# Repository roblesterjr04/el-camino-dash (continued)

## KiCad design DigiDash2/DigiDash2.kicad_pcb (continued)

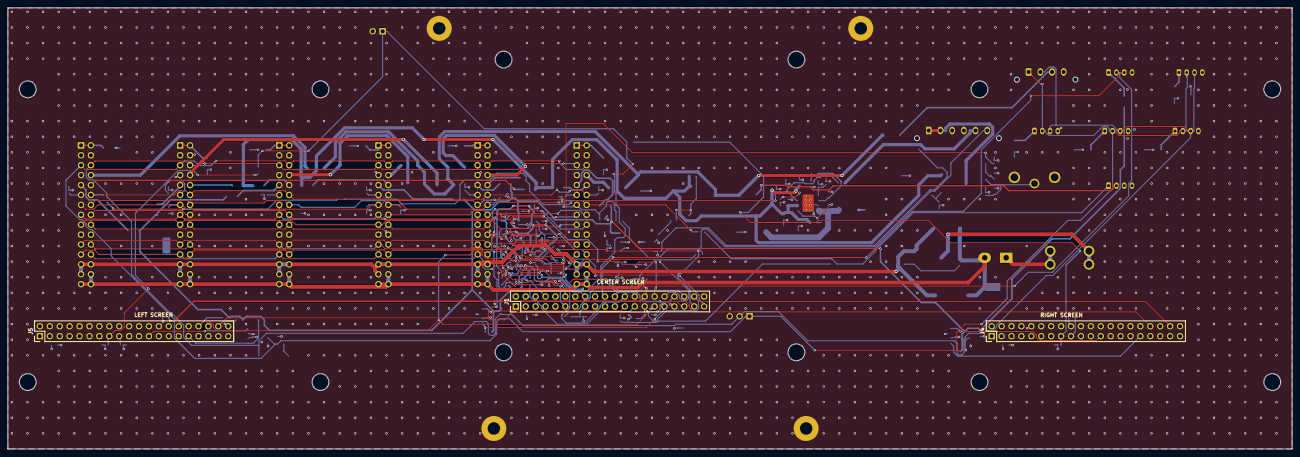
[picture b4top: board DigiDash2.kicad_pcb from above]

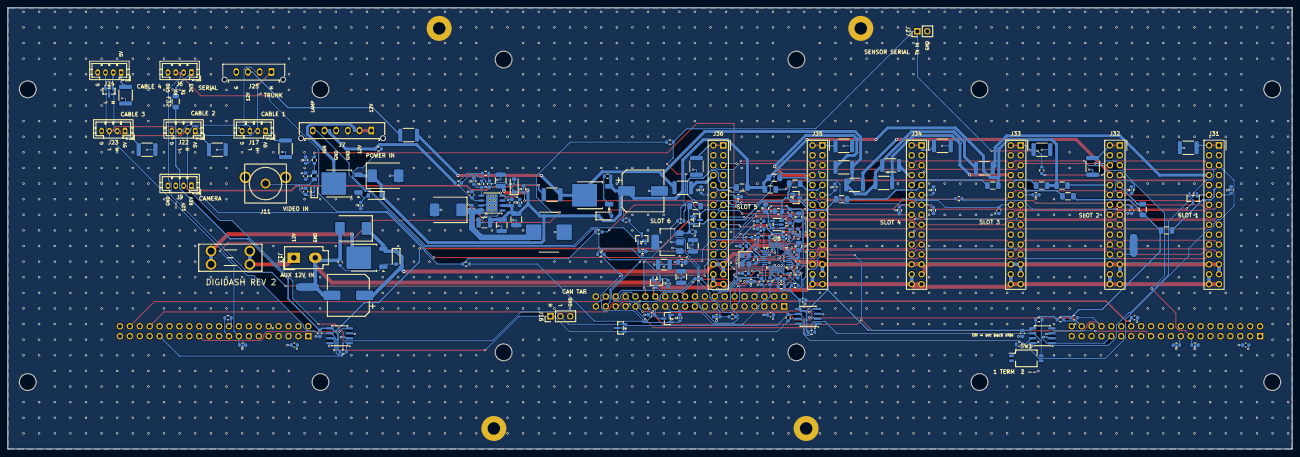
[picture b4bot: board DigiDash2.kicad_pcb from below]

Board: 4 copper layers, 329.0 x 113.0 mm, 197 parts (182 on the bottom side), 126 nets.

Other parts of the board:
H5, H6, H7, H8, H9, H10, H11, H12, H13, H14, H15, H16: M4 screen; MountingHole_4.3mm_M4

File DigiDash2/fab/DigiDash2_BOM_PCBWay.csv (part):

Item #,Designator,Qty,Manufacturer,Mfg Part #,Description / Value,Package/Footprint,Type,Side,Your Instructions / Notes
1,C1 C18,2,Honor,RYRVT63V100UF10*10,"100u 63V: Aluminium electrolytic 100 uF 63 V, SMD",10 x 10.2 mm SMD,SMD,Bottom,63 V: above the SMCJ33A clamp (about 53 V). Panasonic EEE-FK1J101P (AEC-Q200) is the equal
2,C2 C3 C4 C5,4,Murata,GRM32ER72A225KA35L,2.2u 100V: Capacitor 2.2u X7R 100 V,1210,SMD,Bottom,
3,C6 C7 C19 C20 C21 C22 C23 C24 C25 C26 C27 C28 C35 C36 C37 C38 C40 C41,18,Samsung,CL10B104KB8NNNC,100n: Capacitor 100n X7R 50 V,0603,SMD,Bottom,
4,C8 C9 C10,3,Samsung,CL32A476KPJNNNE,47u 10V: Capacitor 47u X5R 10 V,1210,SMD,Bottom,
5,C11,1,Samsung,CL10B472KB8NNNC,4.7n: Capacitor 4.7n X7R 50 V,0603,SMD,Bottom,
6,C12,1,Samsung,CL10C470JB8NNNC,47p: Capacitor 47p C0G 50 V,0603,SMD,Bottom,
7,C13 C14 C17 C39,4,Samsung,CL21B106KOQNNNE,10u: Capacitor 10u X7R 16 V,0805,SMD,Bottom,
8,C15 C31 C32 C33,4,Samsung,CL10B105KO8NNNC,1u: Capacitor 1u X7R 16 V,0603,SMD,Bottom,
9,C16,1,Samsung,CL21A475KOFNNNE,4.7u: Capacitor 4.7u X5R 16 V,0805,SMD,Bottom,
10,C29 C30,2,Samsung,CL10C330JB8NNNC,33p: Capacitor 33p C0G 50 V,0603,SMD,Bottom,Y3 load caps: 2 x (20 pF CL - about 4 pF stray)
11,C34,1,Samsung,CL10A225KO8NNNC,2.2u: Capacitor 2.2u X5R 16 V,0603,SMD,Bottom,
12,D2 D3,2,onsemi,NUP2105LT1G,NUP2105L: CAN bus ESD clamp,SOT-23,SMD,Bottom,
13,D4 D8 D9,3,Diodes Inc,BZT52C15-7-F,BZT52C15: Zener 15 V,SOD-123,SMD,Bottom,
14,D5 D10,2,Littelfuse,SMCJ33A,"SMCJ33A: TVS 33 V standoff, unidirectional, 1500 W",SMC,SMD,Bottom,
15,D6,1,Diodes Inc,B560C-13-F,B560C: Schottky 5 A 60 V,SMC,SMD,Bottom,
16,D7,1,Diodes Inc,BZT52C5V1-7-F,BZT52C5V1: Zener 5.1 V,SOD-123,SMD,Bottom,
17,D11,1,Nexperia,"PESD5V0S1BA,115","PESD5V0S1BA: ESD clamp 5 V, bidirectional",SOD-323,SMD,Bottom,
18,D12 D13 D14,3,Nexperia,"BAT54S,215","BAT54S: Dual Schottky, series",SOT-23,SMD,Bottom,
19,F1,1,Keystone,3568,"5A mini blade: Fuse holder, mini blade (ATM), PCB",THT,THT,Bottom,Holder only; fit a 5 A mini blade fuse (Littelfuse 0297005.WXNV) after soldering if supplied
20,F2 F3 F4 F5 F6 F8 F9 F12 F13 F16 F17 F20 F21 F24 F25 F28 F29,17,PTTC,SMD1812P050TF/30,"PTC 0.5A: PTC 0.5 A hold, 30 V",1812,SMD,Bottom,30 V part on the 5 V and the 12 V lines alike
21,F7,1,Littelfuse,1812L110/33MR,"PTC 1.1A: PTC 1.1 A hold, 33 V",1812,SMD,Bottom,
22,F10 F14 F18 F22 F26 F30 F32,7,Littelfuse,1206L010/60WR,"PTC 0.1A: PTC 0.1 A hold, 60 V",1206,SMD,Bottom,
23,F11 F15 F19 F23 F27 F31,6,Bourns,MF-NSMF020X-2,"PTC 0.2A: PTC 0.2 A hold, 30 V, AEC-Q200",1206,SMD,Bottom,On the battery line: 30 V part
24,FB1,1,Murata,BLM18KG601SN1D,600R: Ferrite bead 600 R at 100 MHz,0603,SMD,Bottom,
25,J1,1,XFCN,PZ254V-12-40P,"Center Screen - Master: Pin header 2 x 20, 2.54 mm, vertical (male; the screen has the 40-pin socket)",THT 2x20,THT,Top,"FRONT side (screen side), the only parts on the front"
26,J4,1,XFCN,PZ254V-12-40P,"Right Screen: Pin header 2 x 20, 2.54 mm, vertical (male; the screen has the 40-pin socket)",THT 2x20,THT,Top,"FRONT side (screen side), the only parts on the front"
27,J5,1,XFCN,PZ254V-12-40P,"Left Screen: Pin header 2 x 20, 2.54 mm, vertical (male; the screen has the 40-pin socket)",THT 2x20,THT,Top,"FRONT side (screen side), the only parts on the front"
28,J6,1,JST,B4B-PH-K-S(LF)(SN),"Serial: JST PH header, 4 pin, vertical",THT,THT,Bottom,
29,J7,1,Molex,43650-0615,"Vehicle power: Micro-Fit 3.0 header, 6 pin, 1 row, vertical",THT,THT,Bottom,
30,J9,1,JST,B4B-PH-K-S(LF)(SN),"Backup Camera: JST PH header, 4 pin, vertical",THT,THT,Bottom,
31,J11,1,Same Sky,RCJ-024,"Video in: RCA jack, vertical, yellow (video)",THT,THT,Bottom,
32,J13,1,Molex,39-28-1023,"AUX 12V in: Mini-Fit Jr header 5566-02A, 2 pin, vertical, no pegs",THT,THT,Bottom,
33,J16,1,Sullins,PRPC003SAAN-RC,"CAN debug: Pin header 1 x 3, 2.54 mm, vertical",THT 1x3,THT,Bottom,
34,J17,1,JST,B4B-PH-K-S(LF)(SN),"Cable port 1: JST PH header, 4 pin, vertical",THT,THT,Bottom,
35,J22,1,JST,B4B-PH-K-S(LF)(SN),"Cable port 2: JST PH header, 4 pin, vertical",THT,THT,Bottom,
36,J23,1,JST,B4B-PH-K-S(LF)(SN),"Cable port 3: JST PH header, 4 pin, vertical",THT,THT,Bottom,
37,J24,1,JST,B4B-PH-K-S(LF)(SN),"Cable port 4: JST PH header, 4 pin, vertical",THT,THT,Bottom,
38,J25,1,Molex,43650-0415,"Trunk port: Micro-Fit 3.0 header, 4 pin, 1 row, vertical",THT,THT,Bottom,
39,J27,1,Sullins,PRPC002SAAN-RC,"Sensor serial in: Pin header 1 x 2, 2.54 mm, vertical",THT 1x2,THT,Bottom,
40,J31,1,Connfly,DS1023-2*15SF11,"Slot 1: Socket 2 x 15, 2.54 mm, female, vertical, 8.5 mm insulator (Sullins PPTC152LFBN-RC equal)",THT 2x15,THT,Bottom,Pin 1 = square pad. Seat flat: the cards plug in square to the board
41,J32,1,Connfly,DS1023-2*15SF11,"Slot 2: Socket 2 x 15, 2.54 mm, female, vertical, 8.5 mm insulator (Sullins PPTC152LFBN-RC equal)",THT 2x15,THT,Bottom,Pin 1 = square pad. Seat flat: the cards plug in square to the board
42,J33,1,Connfly,DS1023-2*15SF11,"Slot 3: Socket 2 x 15, 2.54 mm, female, vertical, 8.5 mm insulator (Sullins PPTC152LFBN-RC equal)",THT 2x15,THT,Bottom,Pin 1 = square pad. Seat flat: the cards plug in square to the board
43,J34,1,Connfly,DS1023-2*15SF11,"Slot 4: Socket 2 x 15, 2.54 mm, female, vertical, 8.5 mm insulator (Sullins PPTC152LFBN-RC equal)",THT 2x15,THT,Bottom,Pin 1 = square pad. Seat flat: the cards plug in square to the board
44,J35,1,Connfly,DS1023-2*15SF11,"Slot 5: Socket 2 x 15, 2.54 mm, female, vertical, 8.5 mm insulator (Sullins PPTC152LFBN-RC equal)",THT 2x15,THT,Bottom,Pin 1 = square pad. Seat flat: the cards plug in square to the board
45,J36,1,Connfly,DS1023-2*15SF11,"Slot 6: Socket 2 x 15, 2.54 mm, female, vertical, 8.5 mm insulator (Sullins PPTC152LFBN-RC equal)",THT 2x15,THT,Bottom,Pin 1 = square pad. Seat flat: the cards plug in square to the board
46,L1,1,COILMX,MS1050-6R8M,"6.8u: Inductor 6.8 uH, Isat 14 A, Irms 8.5 A, molded shielded",11.2 x 10 mm,SMD,Bottom,"Replaces Wurth 7443551720 (7.2 uH, WE-HCI 1050): the land pattern changed with it"
47,Q1 Q3 Q4,3,onsemi,MMBT3904LT1G,MMBT3904: NPN 40 V,SOT-23,SMD,Bottom,
48,Q2 Q5 Q6,3,Vishay,SUD50P04-08-GE3,"SUD50P04-08: P-MOSFET 40 V, 8 mOhm",TO-252 (DPAK),SMD,Bottom,
49,R1 R8 R11 R12 R15 R16 R17 R22 R23 R24 R25 R26 R28 R30 R36 R37 R38 R39,18,Yageo,RC0603FR-0710KL,10k: Resistor 10k 1%,0603,SMD,Bottom,
50,R2,1,Yageo,RC0603FR-07243KL,243k: Resistor 243k 1%,0603,SMD,Bottom,
51,R3,1,Yageo,RC0603FR-0753K6L,53.6k: Resistor 53.6k 1%,0603,SMD,Bottom,
52,R4,1,Yageo,RC0603FR-0710K2L,10.2k: Resistor 10.2k 1%,0603,SMD,Bottom,
53,R5,1,Yageo,RC0603FR-0716K9L,16.9k: Resistor 16.9k 1%,0603,SMD,Bottom,
54,R6,1,Yageo,RC0603FR-07442KL,442k: Resistor 442k 1%,0603,SMD,Bottom,
55,R7,1,Yageo,RC0603FR-0790K9L,90.9k: Resistor 90.9k 1%,0603,SMD,Bottom,
56,R9 R20 R21,3,Yageo,RC0603FR-074K7L,4.7k: Resistor 4.7k 1%,0603,SMD,Bottom,
57,R10 R45,2,Yageo,RC0603FR-0722KL,22k: Resistor 22k 1%,0603,SMD,Bottom,
58,R13 R14 R40 R41,4,Yageo,RC0603FR-071KL,1k: Resistor 1k 1%,0603,SMD,Bottom,
59,R18 R19,2,Yageo,RC0603FR-07120RL,120: Resistor 120 1%,0603,SMD,Bottom,
60,R27 R29 R31,3,Yageo,RC0603FR-0720KL,20k: Resistor 20k 1%,0603,SMD,Bottom,
61,R32 R33,2,Yageo,RC0603FR-0737R4L,37.4: Resistor 37.4 1%,0603,SMD,Bottom,
62,R34,1,Yageo,RC0603FR-0722RL,22: Resistor 22 1%,0603,SMD,Bottom,
63,R35 R47 R49 R51,4,Yageo,RC0603FR-07100KL,100k: Resistor 100k 1%,0603,SMD,Bottom,
64,R42,1,Yageo,RC0603FR-073K3L,3.3k: Resistor 3.3k 1%,0603,SMD,Bottom,
65,R43,1,Yageo,RC0603FR-076K8L,6.8k: Resistor 6.8k 1%,0603,SMD,Bottom,
66,R44,1,Yageo,RC0603FR-0712KL,12k: Resistor 12k 1%,0603,SMD,Bottom,
67,R46 R48,2,Yageo,RC0603FR-0747KL,47k: Resistor 47k 1%,0603,SMD,Bottom,
68,R50 R52,2,Yageo,RC0603FR-0727KL,27k: Resistor 27k 1%,0603,SMD,Bottom,
69,R53,1,Yageo,RC0805JR-070RL,0: Resistor 0 R (jumper),0805,SMD,Bottom,Anti-alias filter L as delivered: swap for a 2.7 uH 0805 to fit the filter
70,SW1,1,KingTek,DSHP02TSGER,"TERM: DIP switch, 2 position, SMD top slide, 1.27 mm pitch",SMD 4.1 x 5.4 mm,SMD,Bottom,Set position 1 (TERM) ON before shipping
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
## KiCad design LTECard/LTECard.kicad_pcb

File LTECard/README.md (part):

# LTE gateway card

A **slot card** for the DigiDash rev 2 board: **80 × 60 mm**, standing on edge in a 2×15 slot, its right-angle header
on the bottom edge (`docs/hardware/accessory_ports.md`, rev 2 section). Spec: [`docs/hardware/lte_card.md`](../docs/hardware/lte_card.md).
It goes in **any slot**. On it:
- an **ESP32-S3-WROOM-1-N16R8** module (16 MB flash, 8 MB octal PSRAM), antenna at the top-left corner
- a **SIMCom A7670 LTE Cat-1 core board** (a ready-made breakout) on two female sockets, 1 × 12 and 1 × 11, 8.5 mm tall
- a **TPS54560B buck** making the core board's 5 V from **AUX 12 V** (slot pins 25–30), with 470 µF bulk at its VIN
- an **MCP2562** CAN transceiver and an **AP7361C-33** 3.3 V regulator, both from the slot's 5 V
- **USB-C** (mid-mount, left edge) to the ESP32-S3's native USB, **BOOT** and **RESET** buttons, a **debug serial**
  header, two LEDs

CAN node from its slot (`0x14 + (slot − 1)`). Firmware: `docs/hardware/lte_card.md`, "Firmware".

> ## Measure the core board before ordering
>
> The core board's geometry and pin order on this card are **provisional**: they come from the vendor listings, not
> from the board in hand. Check every item, edit the constants, re-run the generators (see [Regenerating](#regenerating)):
>
> 1. **Pin order of both rows.** `CORE_ROW_A` (12 pins, left socket J2) and `CORE_ROW_B` (11 pins, right socket J3) at
>    the top of `generate/gen_sch.py`. The current order is a guess that groups power / control on row A and the UART on
>    row B. The names are the board's silkscreen names; `CORE_NETS` maps them to the card.
> 2. **Which end is pin 1**, and the pin counts per row (12 / 11?): `CORE_PIN1_AT_BOTTOM`, `CORE_ROW_A_N`, `CORE_ROW_B_N`
>    in `generate/gen_pcb.py`. Now: pin 1 of both rows at the bottom (toward the slot), so VIN sits by the 470 µF.
> 3. **Row-to-row spacing**, centre to centre: `CORE_ROW_PITCH` (now 40.64 mm = 16 × 2.54), and whether each row is
>    centred on the board's height (`CORE_ROW_A_DY`, `CORE_ROW_B_DY`).
> 4. **Board outline**: `CORE_W` × `CORE_H` (now 44.45 × 31.75 mm), at `CORE_X0`, `CORE_Y0` (upper right). Nothing
>    is placed under it on the parts side. Check the height: 8.5 mm sockets + 1.6 mm + its tallest part must stay under
>    the 20 mm parts-side limit, and the A7670 and IPEX plug underneath must clear the card (8.5 mm).
> 5. **PEN and RST**: polarity, and whether the board pulls them up (and to what voltage). The card drives PEN through
>    1k with a 100k pull-down (LTE off until the firmware raises it) and RST through 1k.
> 6. **STA and NET levels** (1.8 V from VEXT, 3.3 V from the level shifter, or open-collector LED drive?). They come in
>    through 1k each. If they are 1.8 V, the ESP32 (VIH about 2.5 V) will not read them: add a level shifter or move them
>    to an ADC pin.
> 7. **RTS / CTS direction**: wired the SIMCom way (the module's RTS is an input, the ESP32's RTS output drives it).
> 8. **Where the IPEX antenna socket is**, and that the pigtail reaches the case panel.

| Files | |
| --- | --- |
| `LTECard.kicad_sch` / `.kicad_pcb` / `.kicad_pro` | The card: 80 × 60 mm, 4 layers, parts on the front (two capacitors on the back). KiCad 10 |
| `LTECard_BOM.csv` | Bill of materials |
| `generate/` | Scripts that produced the files (`gen_sch.py`, `gen_pcb.py`, `drc.py`, `sexp.py`; `refs.json` is written by `gen_sch.py`). Copied from `AudioCarrier/generate/` and adapted. Every footprint is stock KiCad 10, so there is no `gen_footprints.py` or `.pretty` library |

## What's on it

```
AUX 12 V (pins 25-27) ─ 3 × 2.2 µF 100 V ─ TPS54560B (400 kHz) ─ 6.8 µH ─ LTE_5V ─┬─ 3 × 47 µF
AUX GND  (pins 28-30) ─────── all of the buck's grounds, the core board's GND ─┘    └─ 470 µF ─ core board VIN × 2
                                                                LTE_5V ─ 22k / 33k ─ GPIO5 (AUX present)
+5 V (pins 1, 2) ─ AP7361C-33 ─ +3V3 ─ ESP32-S3, MCP2562 VIO, core board VTTL (its TXS0108E reference)
ESP32-S3 UART1 TX GPIO41 ──► core RXD     RX GPIO42 ◄── core TXD     RTS GPIO40 ──► core RTS    CTS GPIO39 ◄── core CTS
         DTR GPIO38 ──► core DTR          RI GPIO21 ◄── core RI      (no pull-ups: the TXS0108E does not like them)
         PEN GPIO11 ─ 1k ─► core PEN (100k pull-down)   RST GPIO12 ─ 1k ─► core RST
         STA GPIO13 ◄─ 1k ─ core STA                    NET GPIO14 ◄─ 1k ─ core NET
CAN: GPIO9 TX / GPIO10 RX ── MCP2562 (VDD 5 V, VIO 3.3 V, STBY low, no termination) ── pins 5 / 6
Slot ID (pin 11): 10k to 3.3 V here, the slot's resistor to GND on the main board ──► GPIO4 (ADC1)
USB-C D+ / D- ── USBLC6-2SC6 ── GPIO20 / GPIO19 (native USB); CC1 / CC2 5.1k to GND; VBUS only to the clamp
```

### ESP32-S3 pins

| GPIO | Function | GPIO | Function |
| --- | --- | --- | --- |
| 41 | UART1 TX → core RXD | 9 | CAN TX (TWAI) |
| 42 | UART1 RX ← core TXD | 10 | CAN RX (through 1k) |
| 40 | UART1 RTS → core RTS | 4 | Slot ID (ADC1_CH3) |
| 39 | UART1 CTS ← core CTS | 5 | AUX present (ADC1_CH4): 3.0 V with the buck running |
| 38 | DTR out (hold low) | 1 | LED D1, LTE |
| 21 | RI in | 2 | LED D2, Wi-Fi |
| 11 | PEN out (1k, 100k pull-down) | 19 / 20 | USB D− / D+ |
| 12 | RST out (1k) | 43 / 44 | TXD0 / RXD0, debug serial J5 |
| 13 | STA in (1k) | 0 | BOOT button (strap) |
| 14 | NET in (1k) | EN | RESET button, 10k / 1 µF |

Not used: the strapping pins GPIO3, 45, 46 (and GPIO0 except for BOOT), the octal-PSRAM pins GPIO35–37, GPIO47 / 48.
UART1 runs through the GPIO matrix (its default pins are the USB pins).

### Grounds: AUX GND is not GND

On the main board AUX GND meets GND **only at NT1**, at the power entry. If this card joined them too, the two would
form a loop through NT1, and AUX return current (this card's and every other card's) would share the slot GND pins and
the main board's logic ground. So **the card does not join them**: there is no net tie.
- **AUX side (AUX_GND):** the buck and everything around it, the 470 µF, and the core board's GND pins. AUX_GND has
  its own pours on F, In2 and B over the buck area (stitched with AUX_GND vias), 0.8 mm tracks elsewhere.
- **Logic side (GND):** the ESP32, CAN, USB, LDO. In1 is a solid GND plane under the whole card, the buck included
  (it is only a reference plane there: nothing of the AUX side connects to it).
- Only logic signals cross between the two (UART, control lines through 1k, the AUX-present divider). The offset
  between the grounds is the voltage drop on the main board between the card and NT1 (tens of mV), well inside the
  logic margins.
- **On the bench:** a card powered without the main board needs AUX GND and GND joined at the supply, or the core
  board's ground floats.

## Slot connector (J1)

| Pins | Signal | Used |
| --- | --- | --- |
| 1 / 2 | +5 V | ESP32-S3, CAN, 3.3 V regulator |
| 3 / 4, 7, 19 / 20 | GND | logic ground |
| 5 / 6 | CANH / CANL | MCP2562 |
| 11 | slot ID | 10k to 3.3 V, GPIO4 |
| 25 / 26 / 27 | AUX 12 V | the LTE buck |
| 28 / 29 / 30 | AUX GND | the LTE buck and core board return |
| 8, 9, 10, 12–18, 21–24 | switched / constant 12 V, 3.3 V, WAKE, LAMP, REV, links, audio bus | not connected |

| Other connectors | | |
| --- | --- | --- |
| J2 | LTE core board row A, 1 × 12 female, 8.5 mm | provisional pin order (see above) |
| J3 | LTE core board row B, 1 × 11 female, 8.5 mm | provisional pin order |
| J4 | USB-C, mid-mount, left edge (Amphenol 12401948E412A) | native USB: flash and serial console. The card is powered from the slot |
| J5 | debug serial, 1 × 3 right angle, left edge | 1 GND, 2 TX0 (to the adapter's RX), 3 RX0. 3.3 V logic, not a supply |
| SW1 / SW2 | RESET / BOOT, beside the USB-C | Flash: hold BOOT, tap RESET (only needed if the USB-JTAG is not answering) |

## Board

- **Outline:** 80 × 60 mm, no mounting holes. A notch in the left edge for the mid-mount USB-C (it is in the
  footprint's own Edge.Cuts).
- **Slot header (J1):** placed exactly as on the audio card (`PinHeader_2x15_P2.54mm_Horizontal`, pin 1 17.78 mm right
  of the centre, the pins counting to the left, its body on the bottom edge); `gen_pcb.py` checks the orientation from
  the pads.
- **Top left:** the module, antenna end on the top edge at the corner, with the stock footprint's keep-out (no copper,
  vias or parts on any layer, 15 mm to its right; nothing on the back under it). Keep metal away from that corner of
  the case. The core board starts right of the keep-out.
- **Top right:** the core board on its sockets. Nothing is placed under it.
- **Left edge:** LEDs (under the module), USB-C, RESET / BOOT, the debug header.
- **Bottom:** the buck by the AUX pins (25–30), the 470 µF under the core board's VIN pins, the CAN transceiver and
  the 3.3 V regulator by pins 1–6.
- **Back:** only the module's 22 µF / 100 nF (C3 / C4), behind its 3V3 pin: there is no room between the module's pads
  and the edge.
- **Layers:** F signal, In1 solid GND, In2 signal / pours, B signal. 0.2 mm tracks, 0.13 mm clearance, 0.6 / 0.3 mm
  vias (as the audio card). Net classes as on the main board: Power 0.3 mm (GND, +5V, +3V3); Aux 1.0 mm / 0.2 mm
  (AUX12, LTE_5V); AuxGnd 0.8 mm / 0.2 mm (AUX_GND); Switch 1.0 mm / 0.2 mm (BUCK_SW).
- **Antenna (LTE):** nothing RF on the card: an IPEX-to-SMA pigtail from the core board to the case panel.

## Status

**Schematic: done** (63 parts, ERC: no errors; the warnings are off-grid pins and the generated `LTECard` symbol
library not being in the library table). **PCB: placed and routed** by `gen_pcb.py` (Freerouting 1.9.0 plus the
script's finisher and stitching, no hand edits). DRC with the schematic parity check (2026-10-01): **0 errors,
0 unconnected**, warnings only: 21 silkscreen-past-the-edge (J1, J4 and J5 stick out of the outline on purpose), 2 LED
legend / LED outline overlaps, and the module footprint differing from the library (its 0.2 mm ground-pad vias are
opened to 0.3 mm). Three short pieces of the switch node were necked to 0.6 mm by the router at the pads.
**Not ordered:** the core board items above come first.

Also check before ordering:
- the buck: L1's ratings (Isat ≥ 5 A, Irms ≥ 3 A); the compensation is the main board's (TI typical application for
  7.2 µH and 3 × 47 µF) with a 6.8 µH inductor and the 470 µF electrolytic added at the load: check the loop (TI
  WEBENCH, or a load-step test) once the parts are known.
- pin 1 of J1 against the main board's slot in KiCad's 3D viewer, and the USB-C notch against the case.
- the module's ground-pad vias were opened from the footprint's 0.2 mm to 0.3 mm drills (the board's minimum).

## Regenerating

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
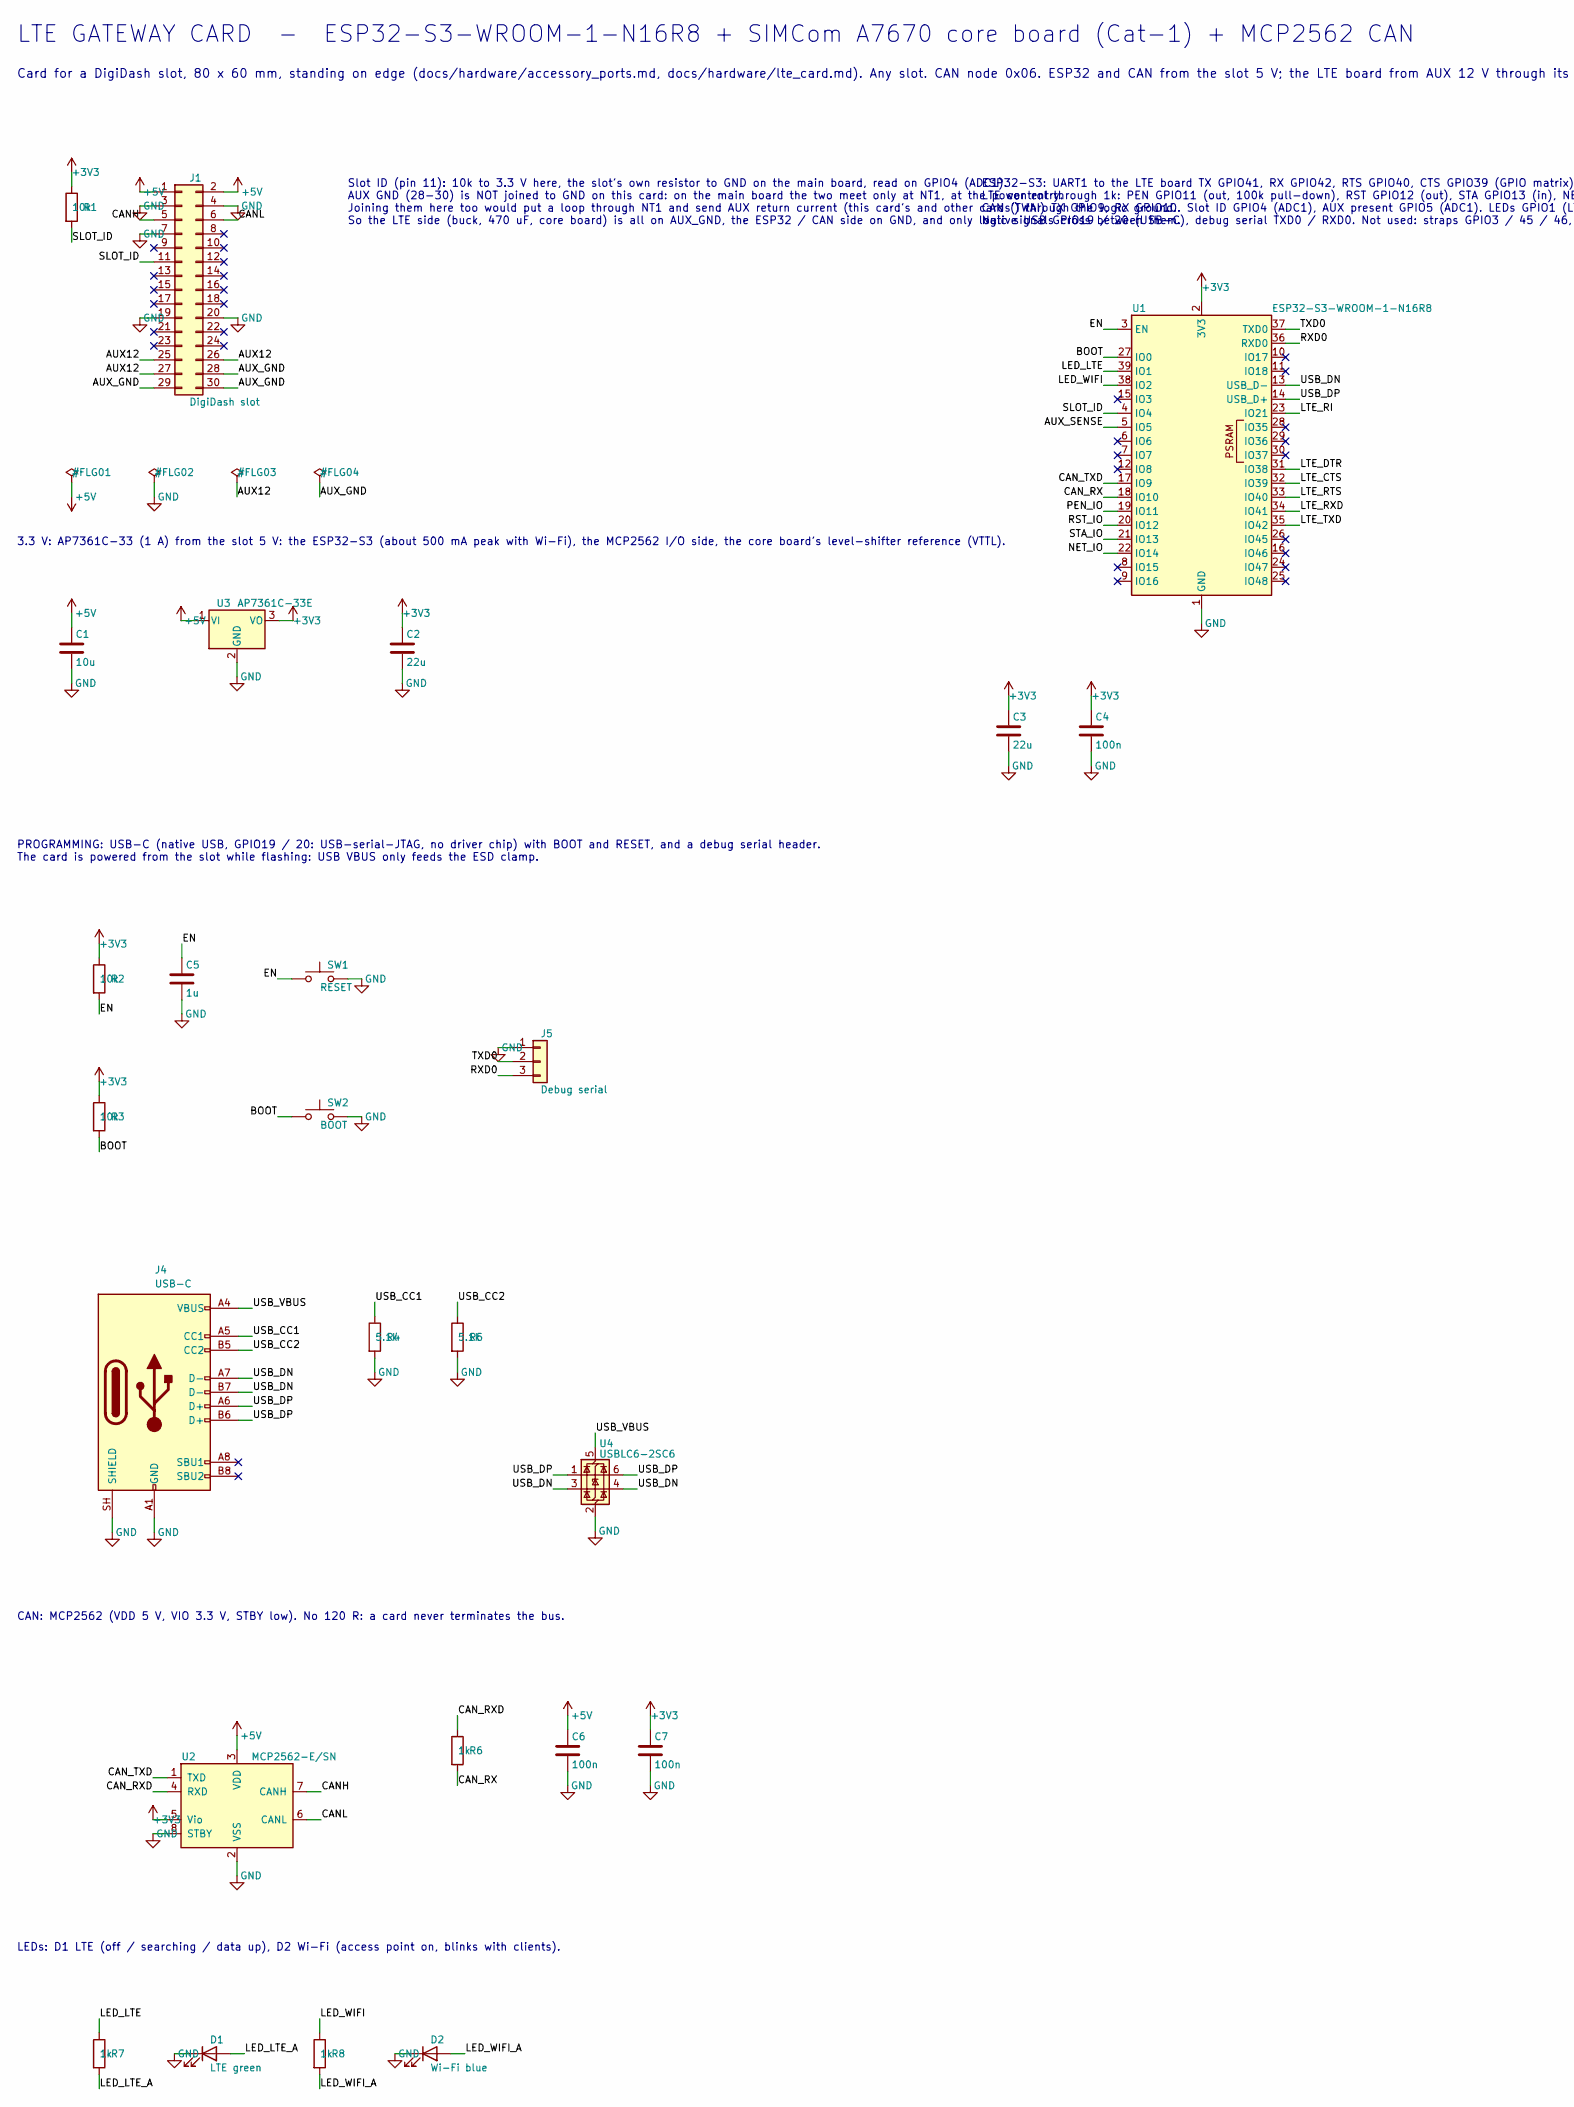
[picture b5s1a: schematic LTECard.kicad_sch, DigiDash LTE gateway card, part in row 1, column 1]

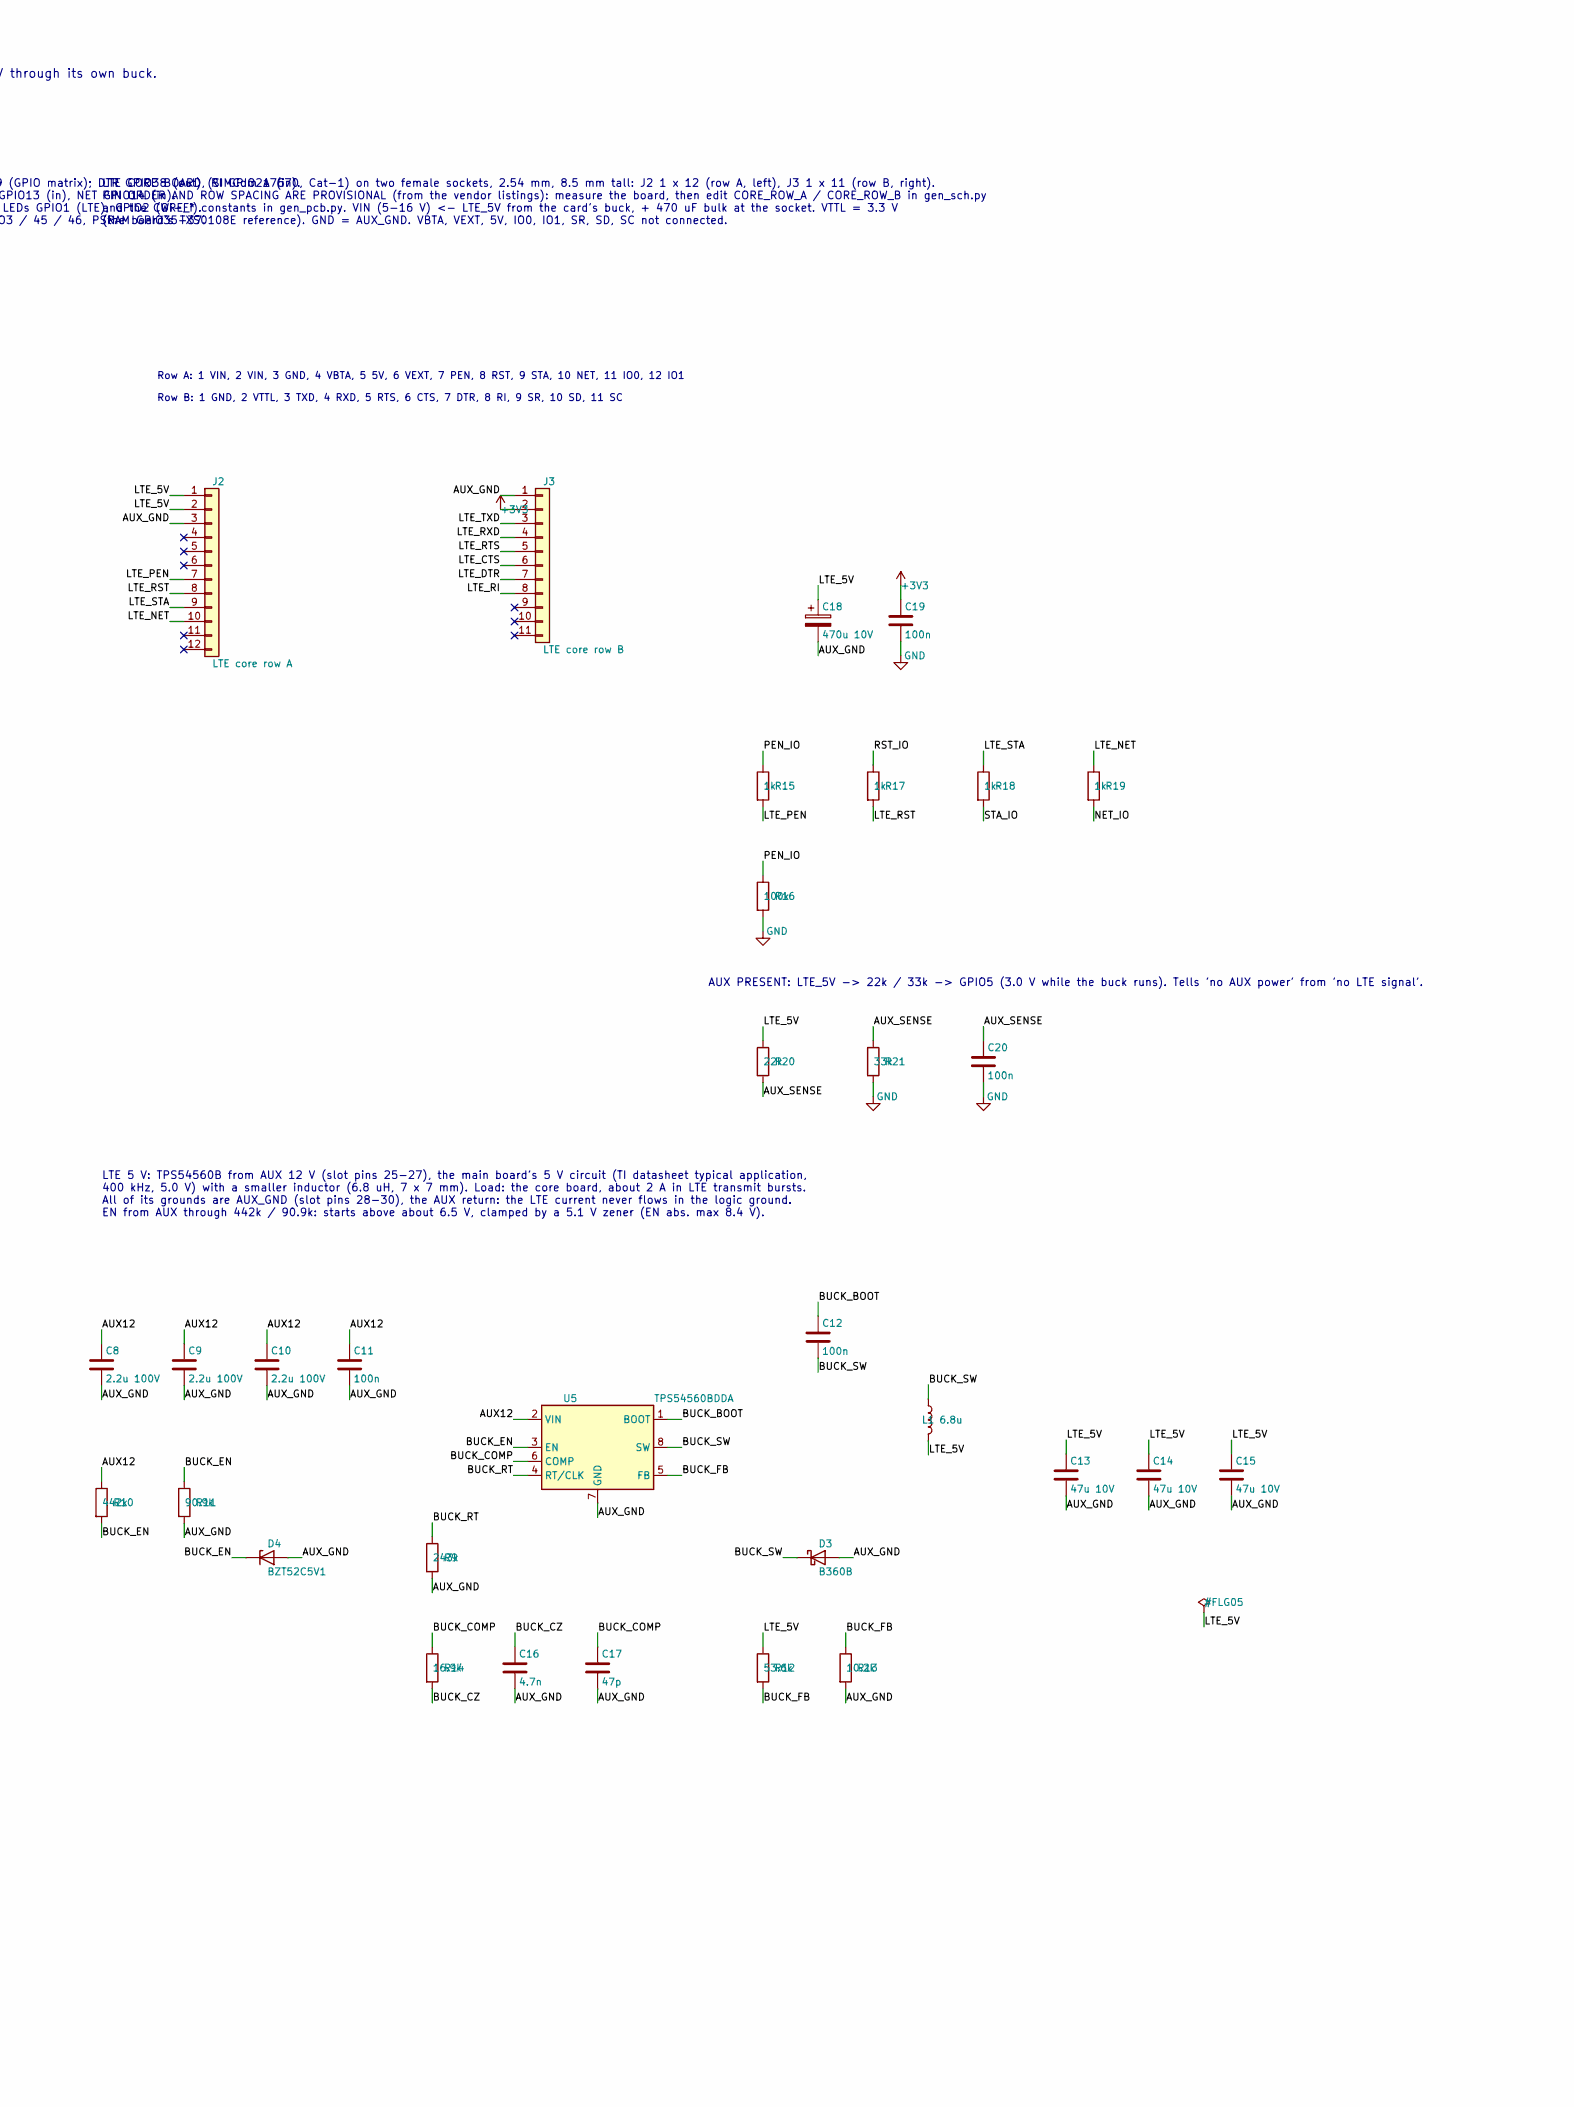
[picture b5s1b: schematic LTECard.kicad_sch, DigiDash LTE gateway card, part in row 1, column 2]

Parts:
C1: 10u; C_0805_2012Metric
C2, C3: 22u; C_0805_2012Metric
C4, C6, C7, C12, C19, C20: 100n; C_0603_1608Metric
C5: 1u; C_0603_1608Metric
C8, C9, C10: 2.2u 100V; C_1210_3225Metric
C11: 100n; C_0805_2012Metric
C13, C14, C15: 47u 10V; C_1210_3225Metric
C16: 4.7n; C_0603_1608Metric
C17: 47p; C_0603_1608Metric
C18: 470u 10V; CP_Elec_8x10
D1: LTE green; LED_0603_1608Metric
D2: Wi-Fi blue; LED_0603_1608Metric
D3: B360B; D_SMB
D4: BZT52C5V1; D_SOD-123
J1: DigiDash slot; PinHeader_2x15_P2.54mm_Horizontal
J2: LTE core row A; PinSocket_1x12_P2.54mm_Vertical
J3: LTE core row B; PinSocket_1x11_P2.54mm_Vertical
J4: USB-C; USB_C_Receptacle_Amphenol_12401948E412A
J5: Debug serial; PinHeader_1x03_P2.54mm_Horizontal
L1: 6.8u; L_Bourns_SRP7028A_7.3x6.6mm
R1, R2, R3: 10k; R_0603_1608Metric
R4, R5: 5.1k; R_0603_1608Metric
R6, R7, R8, R15, R17, R18, R19: 1k; R_0603_1608Metric
R9: 243k; R_0603_1608Metric
R10: 442k; R_0603_1608Metric
R11: 90.9k; R_0603_1608Metric
R12: 53.6k; R_0603_1608Metric
R13: 10.2k; R_0603_1608Metric
R14: 16.9k; R_0603_1608Metric
R16: 100k; R_0603_1608Metric
R20: 22k; R_0603_1608Metric
R21: 33k; R_0603_1608Metric
SW1: RESET; SW_SPST_PTS810
SW2: BOOT; SW_SPST_PTS810
U1: ESP32-S3-WROOM-1-N16R8; ESP32-S3-WROOM-1
U2: MCP2562-E/SN; SOIC-8_3.9x4.9mm_P1.27mm
U3: AP7361C-33E; SOT-223-3_TabPin2
U4: USBLC6-2SC6; SOT-23-6
U5: TPS54560BDDA; TI_SO-PowerPAD-8_ThermalVias

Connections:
+3V3: C2.1, C3.1, C4.1, C7.1, C19.1, J3.2, R1.1, R2.1, R3.1, U1.2 (3V3), U2.5 (Vio), U3.3 (VO)
+5V: C1.1, C6.1, J1.1, J1.2, U2.3 (VDD), U3.1 (VI)
/AUX12: C8.1, C9.1, C10.1, C11.1, J1.25, J1.26, J1.27, R10.1, U5.2 (VIN)
/AUX_GND: C8.2, C9.2, C10.2, C11.2, C13.2, C14.2, C15.2, C16.2, C17.2, C18.2, D3.2 (A), D4.2 (A), J1.28, J1.29, J1.30, J2.3, J3.1, R9.2, R11.2, R13.2, U5.7 (GND), U5.9 (GND)
/AUX_SENSE: C20.1, R20.2, R21.1, U1.5 (IO5)
/BOOT: R3.2, SW2.1, U1.27 (IO0)
/BUCK_BOOT: C12.1, U5.1 (BOOT)
/BUCK_COMP: C17.1, R14.1, U5.6 (COMP)
/BUCK_CZ: C16.1, R14.2
/BUCK_EN: D4.1 (K), R10.2, R11.1, U5.3 (EN)
/BUCK_FB: R12.2, R13.1, U5.5 (FB)
/BUCK_RT: R9.1, U5.4 (RT/CLK)
/BUCK_SW: C12.2, D3.1 (K), L1.1, U5.8 (SW)
/CANH: J1.5, U2.7 (CANH)
/CANL: J1.6, U2.6 (CANL)
/CAN_RX: R6.2, U1.18 (IO10)
/CAN_RXD: R6.1, U2.4 (RXD)
/CAN_TXD: U1.17 (IO9), U2.1 (TXD)
/EN: C5.1, R2.2, SW1.1, U1.3 (EN)
/LED_LTE: R7.1, U1.39 (IO1)
/LED_LTE_A: D1.2 (A), R7.2
/LED_WIFI: R8.1, U1.38 (IO2)
/LED_WIFI_A: D2.2 (A), R8.2
/LTE_5V: C13.1, C14.1, C15.1, C18.1, J2.1, J2.2, L1.2, R12.1, R20.1
/LTE_CTS: J3.6, U1.32 (IO39)
/LTE_DTR: J3.7, U1.31 (IO38)
/LTE_NET: J2.10, R19.1
/LTE_PEN: J2.7, R15.2
/LTE_RI: J3.8, U1.23 (IO21)
/LTE_RST: J2.8, R17.2
/LTE_RTS: J3.5, U1.33 (IO40)
/LTE_RXD: J3.4, U1.34 (IO41)
/LTE_STA: J2.9, R18.1
/LTE_TXD: J3.3, U1.35 (IO42)
/NET_IO: R19.2, U1.22 (IO14)
/PEN_IO: R15.1, R16.1, U1.19 (IO11)
/RST_IO: R17.1, U1.20 (IO12)
/RXD0: J5.3, U1.36 (RXD0)
/SLOT_ID: J1.11, R1.2, U1.4 (IO4)
/STA_IO: R18.2, U1.21 (IO13)
/TXD0: J5.2, U1.37 (TXD0)
/USB_CC1: J4.A5 (CC1), R4.1
/USB_CC2: J4.B5 (CC2), R5.1
/USB_DN: J4.A7 (D-), J4.B7 (D-), U1.13 (USB_D-), U4.3 (I/O2), U4.4 (I/O2)
/USB_DP: J4.A6 (D+), J4.B6 (D+), U1.14 (USB_D+), U4.1 (I/O1), U4.6 (I/O1)
/USB_VBUS: J4.A4 (VBUS), J4.A9 (VBUS), J4.B4 (VBUS), J4.B9 (VBUS), U4.5 (VBUS)
GND: C1.2, C2.2, C3.2, C4.2, C5.2, C6.2, C7.2, C19.2, C20.2, D1.1 (K), D2.1 (K), J1.3, J1.4, J1.7, J1.19, J1.20, J4.A1 (GND), J4.A12 (GND), J4.B1 (GND), J4.B12 (GND), J4.SH (SHIELD), J5.1, R4.2, R5.2, R16.2, R21.2, SW1.2, SW2.2, U1.1 (GND), U1.40 (GND), U1.41 (GND), U2.2 (VSS), U2.8 (STBY), U3.2 (GND), U4.2 (GND)

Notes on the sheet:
LTE GATEWAY CARD - ESP32-S3-WROOM-1-N16R8 + SIMCom A7670 core board (Cat-1) + MCP2562 CAN
Card for a DigiDash slot, 80 x 60 mm, standing on edge (docs/hardware/accessory_ports.md, docs/hardware/lte_card.md). Any slot. CAN node 0x06. ESP32 and CAN from the slot 5 V; the LTE board from AUX 12 V through its own buck.
Slot ID (pin 11): 10k to 3.3 V here, the slot's own resistor to GND on the main board, read on GPIO4 (ADC1). AUX GND (28-30) is NOT joined to GND on this card: on the main board the two meet only at NT1, at the power entry. Joining them here too would put a loop through NT1 and send AUX return curr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
3.3 V: AP7361C-33 (1 A) from the slot 5 V: the ESP32-S3 (about 500 mA peak with Wi-Fi), the MCP2562 I/O side, the core board's level-shifter reference (VTTL).
ESP32-S3: UART1 to the LTE board TX GPIO41, RX GPIO42, RTS GPIO40, CTS GPIO39 (GPIO matrix); DTR GPIO38 (out), RI GPIO21 (in). LTE control through 1k: PEN GPIO11 (out, 100k pull-down), RST GPIO12 (out), STA GPIO13 (in), NET GPIO14 (in). CAN (TWAI) TX GPIO9, RX GPIO10. Slot ID GPIO4 (ADC1), AUX pres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
PROGRAMMING: USB-C (native USB, GPIO19 / 20: USB-serial-JTAG, no driver chip) with BOOT and RESET, and a debug serial header. The card is powered from the slot while flashing: USB VBUS only feeds the ESD clamp.
CAN: MCP2562 (VDD 5 V, VIO 3.3 V, STBY low). No 120 R: a card never terminates the bus.
LEDs: D1 LTE (off / searching / data up), D2 Wi-Fi (access point on, blinks with clients).
LTE 5 V: TPS54560B from AUX 12 V (slot pins 25-27), the main board's 5 V circuit (TI datasheet typical application, 400 kHz, 5.0 V) with a smaller inductor (6.8 uH, 7 x 7 mm). Load: the core board, about 2 A in LTE transmit bursts. All of its grounds are AUX_GND (slot pins 28-30), the AUX return: t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
LTE CORE BOARD (SIMCom A7670, Cat-1) on two female sockets, 2.54 mm, 8.5 mm tall: J2 1 x 12 (row A, left), J3 1 x 11 (row B, right). PIN ORDER AND ROW SPACING ARE PROVISIONAL (from the vendor listings): measure the board, then edit CORE_ROW_A / CORE_ROW_B in gen_sch.py and the CORE_* constants in g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
Row A: 1 VIN, 2 VIN, 3 GND, 4 VBTA, 5 5V, 6 VEXT, 7 PEN, 8 RST, 9 STA, 10 NET, 11 IO0, 12 IO1
Row B: 1 GND, 2 VTTL, 3 TXD, 4 RXD, 5 RTS, 6 CTS, 7 DTR, 8 RI, 9 SR, 10 SD, 11 SC
AUX PRESENT: LTE_5V -> 22k / 33k -> GPIO5 (3.0 V while the buck runs). Tells 'no AUX power' from 'no LTE signal'.

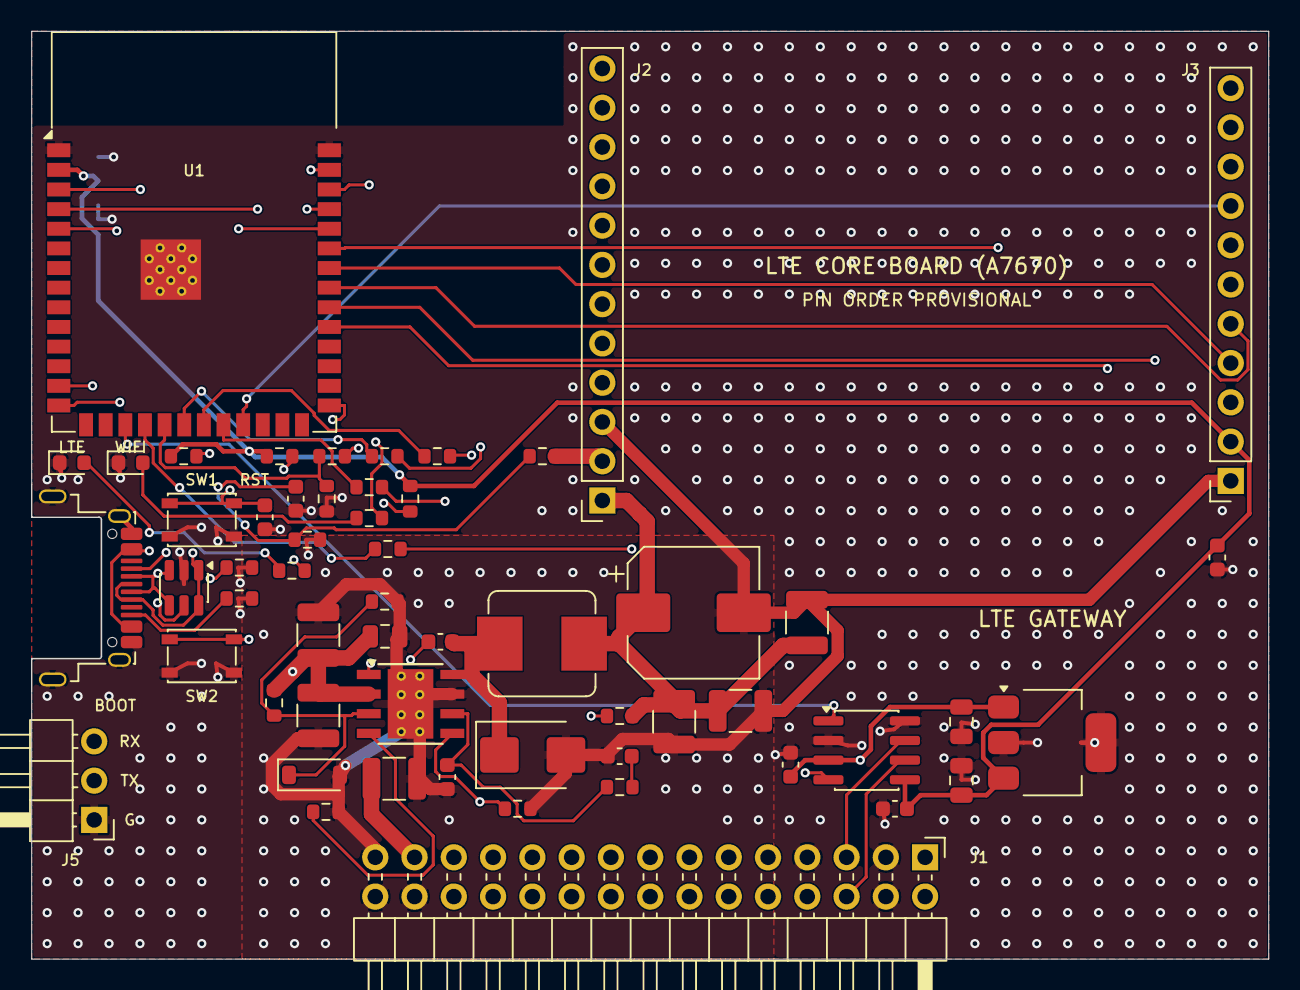
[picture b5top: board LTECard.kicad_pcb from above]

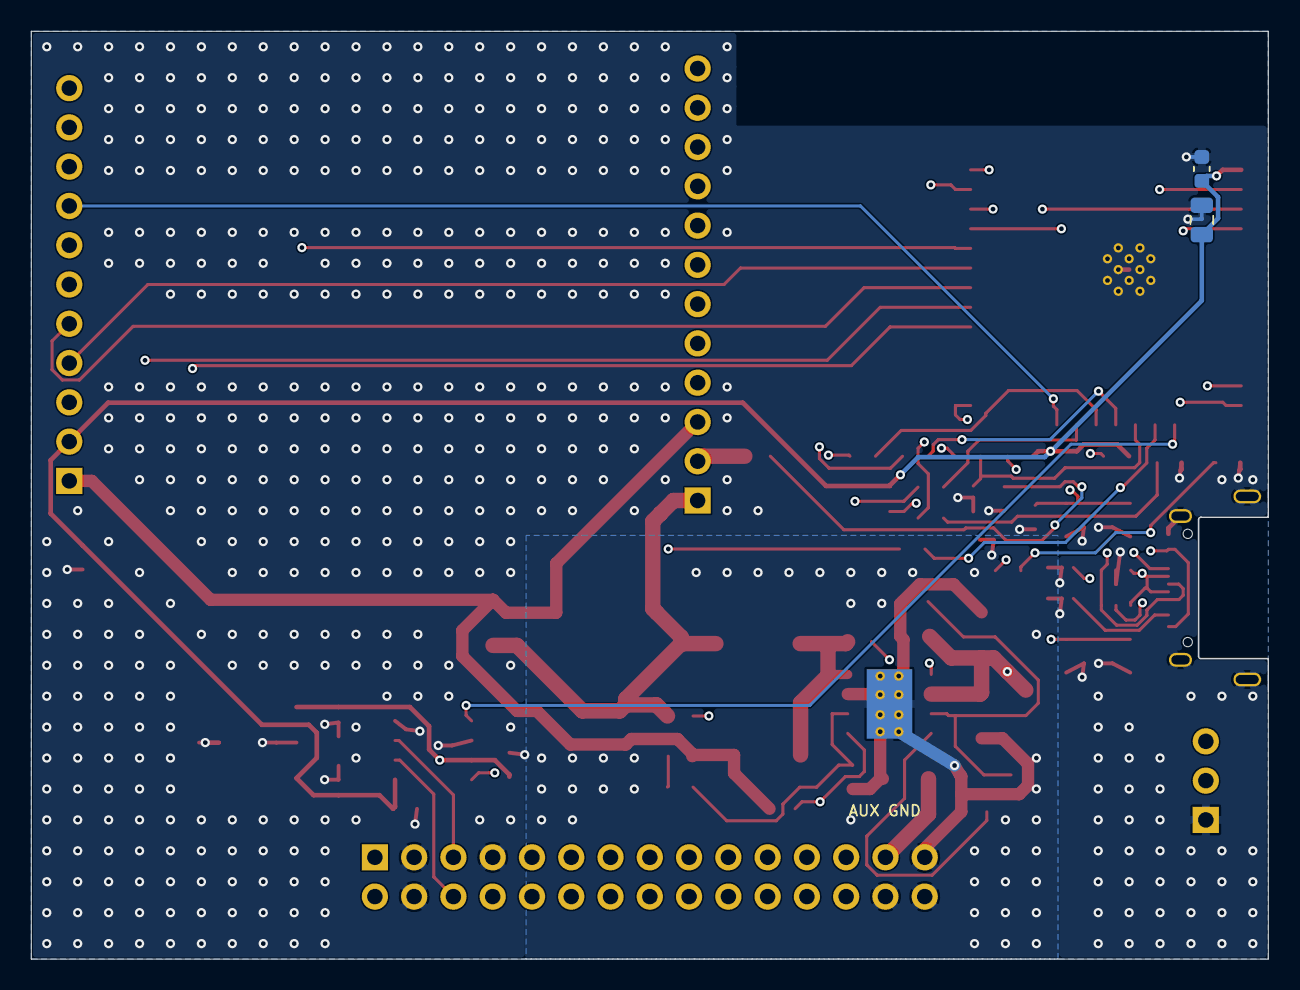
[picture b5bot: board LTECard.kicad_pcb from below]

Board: 4 copper layers, 80.0 x 60.0 mm, 58 parts (2 on the bottom side), 47 nets.

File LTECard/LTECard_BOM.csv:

Qty,Designators,Manufacturer part,Description,Package,Type,Side,Notes
1,C1,10u 0805 ceramic X5R 10 V,10u: U3 input,0805,SMD,Top,
2,C2 C3,22u 0805 ceramic X5R 10 V,22u: U3 output / module supply,0805,SMD,Top/Bottom,C3 on the back behind the module's 3V3 pin
6,C4 C6 C7 C12 C19 C20,100n 0603 ceramic X7R 50 V,"100n: decoupling, buck bootstrap (C12), AUX sense filter (C20)",0603,SMD,Top/Bottom,C4 on the back
1,C11,100n 0805 ceramic X7R 100 V,100n 100 V: buck input HF (AUX 12 V),0805,SMD,Top,
1,C5,1u 0603 ceramic X7R 16 V,1u: EN delay,0603,SMD,Top,
3,C8 C9 C10,2.2u 1210 ceramic X7R 100 V,2.2u 100 V: buck input (TI typical application),1210,SMD,Top,
3,C13 C14 C15,47u 1210 ceramic X5R 10 V,47u: buck output,1210,SMD,Top,
1,C16,4.7n 0603 ceramic X7R 50 V,4.7n: buck compensation,0603,SMD,Top,
1,C17,47p 0603 ceramic C0G 50 V,47p: buck compensation,0603,SMD,Top,
1,C18,"470 uF 10 V (or more) aluminium electrolytic, low ESR, 8 x 10 mm SMD",470u: bulk at the LTE core board VIN,CP_Elec_8x10,SMD,Top,Polarised: + to LTE_5V
1,D1,"LED 0603 green",LTE status LED,0603,SMD,Top,
1,D2,"LED 0603 blue",Wi-Fi LED,0603,SMD,Top,
1,D3,Diodes Inc B360B-13-F,"Schottky 3 A 60 V, buck catch diode",SMB,SMD,Top,
1,D4,BZT52C5V1,"Zener 5.1 V, buck EN clamp",SOD-123,SMD,Top,
1,J1,"Sullins PRPC015DBAN-M71RC (or any 2 x 15, 2.54 mm right-angle male header)","DigiDash slot: pin header 2 x 15, 2.54 mm, right angle (bottom edge)",THT,THT,Top,Pin 1 against the main board slot socket in the 3D viewer before ordering
1,J2,"Female socket 1 x 12, 2.54 mm, 8.5 mm insulator (Sullins PPTC121LFBN-RC or equal)",LTE core board row A,THT,THT,Top,Row spacing and pin order PROVISIONAL (see README)
1,J3,"Female socket 1 x 11, 2.54 mm, 8.5 mm insulator (Sullins PPTC111LFBN-RC or equal)",LTE core board row B,THT,THT,Top,Row spacing and pin order PROVISIONAL (see README)
1,J4,Amphenol 12401948E412A,"USB 2.0 Type-C receptacle, mid-mount (in a notch of the left edge)",SMD + THT shell,SMD,Top,
1,J5,"2.54 mm pin header 1 x 3, right angle",Debug serial (GND TX0 RX0),THT,THT,Top,Left edge
1,L1,Bourns SRP7028A-6R8M (or equal),"6.8 uH shielded, Isat >= 5 A, Irms >= 3 A",7.3 x 6.6 mm,SMD,Top,Check the ratings of the part bought
1,R1,10k 0603 1%,Slot ID pull-up,0603,SMD,Top,
2,R2 R3,10k 0603 1%,EN / BOOT pull-ups,0603,SMD,Top,
2,R4 R5,5.1k 0603 1%,USB-C CC pull-downs,0603,SMD,Top,
1,R6,1k 0603 1%,CAN RX series,0603,SMD,Top,
2,R7 R8,1k 0603 1%,LED series,0603,SMD,Top,
1,R9,243k 0603 1%,Buck RT (400 kHz),0603,SMD,Top,
1,R10,442k 0603 1%,Buck EN divider top,0603,SMD,Top,
1,R11,90.9k 0603 1%,Buck EN divider bottom,0603,SMD,Top,
1,R12,53.6k 0603 1%,Buck feedback top (5.0 V),0603,SMD,Top,
1,R13,10.2k 0603 1%,Buck feedback bottom,0603,SMD,Top,
1,R14,16.9k 0603 1%,Buck compensation,0603,SMD,Top,
4,R15 R17 R18 R19,1k 0603 1%,"PEN, RST, STA, NET series",0603,SMD,Top,
1,R16,100k 0603 1%,PEN pull-down,0603,SMD,Top,
1,R20,22k 0603 1%,AUX present divider top,0603,SMD,Top,
1,R21,33k 0603 1%,AUX present divider bottom,0603,SMD,Top,
2,SW1 SW2,C&K PTS810 SJM 250 SMTR LFS,RESET / BOOT tact switches,SMD,SMD,Top,
1,U1,Espressif ESP32-S3-WROOM-1-N16R8,"ESP32-S3 module, 16 MB flash, 8 MB octal PSRAM, PCB antenna",Module,SMD,Top,Antenna at the top-left corner with the keep-out as placed
1,U2,Microchip MCP2562-E/SN,"CAN FD transceiver, VDD 5 V, VIO 3.3 V",SOIC-8,SMD,Top,
1,U3,Diodes Inc AP7361C-33E-13,LDO 3.3 V 1 A,SOT-223,SMD,Top,
1,U4,ST USBLC6-2SC6,USB ESD clamp,SOT-23-6,SMD,Top,
1,U5,Texas Instruments TPS54560BDDAR,"Buck 4.5-60 V in, 5 A: LTE 5 V from AUX 12 V",SO-8 PowerPAD,SMD,Top,
1,(not on the card),SIMCom A7670 core board (A7670E / A7670SA to suit the region),LTE Cat-1 core board on J2 / J3,Plug-in,,Top,"Plus an IPEX-to-SMA bulkhead pigtail and an external LTE antenna"
